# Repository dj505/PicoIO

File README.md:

# PicoIO
An affordable, simple, and feature-rich PIU controller IO board

## What is this?
The PicoIO is an extension of the [PicoFX](https://github.com/dj505/PicoFX) that's meant for building larger hand controllers or buttonboards. It's possible to build dance pads too, but as this board lacks multiplexing and is made with 5V LED lighting in mind, it's not ideal. I may design a pad IO PCB in the future, though!

**If you're not comfortable with soldering surface mount components,** there is a second board revision in the "PicoFX-THT" directory (gerbers included) that only uses through-hole components. Check the components list to see which parts are required for which PCB!

## Use cases
* Hand controller (10 buttons, 12 if you include test/service)
* Arcade buttonboard, for machines that don't already have a buttonboard (TODO - add support in firmware)
* Simple dance pad (with limitations)
    * No multiplexing support; all sensors will need to be combined into one signal
    * Limited maximum power supply for LEDs; only designed for 10-20 LEDs total, with a maximum of ~0.7A draw
        * This can be bypassed/remedied by using the expansion IO to control external LEDs with their own external power supply and some MOSFETs. I encourage you to be creative!
* Upgrade existing hand controllers, in case of broken/defective/underperforming IO

## THT vs SMD Boards
The PicoIO has two current revisions, one using surface mount components, and one using through-hole components. There are some notable differences between the two!  
* As the dense traces on the through-hole revision were a challenge to route, the traces used for LED power are thinner, which limits the maximum safe current consumption per button LED to around 0.4A or below.
* The surface mount revision of the board has much more room for routing, resulting in thicker power traces that can safely handle roughly 1.2A per button LED.
* The through-hole revision lacks debug headers, but the debug pins on the Pico are still easily accessible. This shouldn't be an issue for anyone anyway, though.

## Components
| Components (per 1 PCB) | Specs | Notes | Recommended Purchase Link | Approximate Min. Cost of Components |
|------------------------|-------|-------|---------------------------|-----------------------------------------|
|1x Raspberry Pi Pico|Any, however WiFi/Bluetooth is currently unsupported|Can be soldered with pin headers or surface mounted.|[Link](https://www.digikey.ca/en/products/detail/raspberry-pi/SC0915/13624793)|$4|
|JST XH connectors|<ul><li>10x 4 Pin</li><li>1x 6 Pin</li><li>1x 3 Pin</li><li>1x 2 Pin</li></ul>|**2.5mm pin pitch.** Designed with vertical headers in mind. Horizontal ones may work but are untested. Recommended purchase link has a minimum order number of 50-100 depending on the connector, but they're still super cheap.|<ul><li>[2 Pin](https://www.lcsc.com/product-detail/Wire-To-Board-Wire-To-Wire-Connector_HCTL-XH-2A_C3012117.html)</li><li>[3 Pin](https://www.lcsc.com/product-detail/Wire-To-Board-Wire-To-Wire-Connector_HCTL-XH-3A_C3012118.html)</li><li>[4 Pin](https://www.lcsc.com/product-detail/Wire-To-Board-Wire-To-Wire-Connector_HCTL-XH-4A_C2908602.html)</li><li>[6 Pin](https://www.lcsc.com/product-detail/Wire-To-Board-Wire-To-Wire-Connector_HCTL-XH-6A_C2908604.html)</li></ul>|$2.50|
|10x BSS138 MOSFET \*|SOT23 Package|Required for button LEDs. Recommendation - buy extras.|[Link](https://www.lcsc.com/product-detail/MOSFETs_Yangzhou-Yangjie-Elec-Tech-BSS138_C400505.html)|$0.40|
|10x 2N7002 MOSFET \*\*|TO-92 Package|Required for button LEDs.|[Link](https://www.lcsc.com/product-detail/MOSFETs_onsemi-2N7002_C124475.html)|$0.40|
|10x Resistors \*|10k Ohm, 0805 Surface Mount|Required for button LEDs. Recommendation - buy extras.|[Link](https://www.lcsc.com/product-detail/Chip-span-style-background-color-ff0-Resistor-span-Surface-Mount_Viking-Tech-AR05DTC1001_C416059.html)|$1|
|10x Resistors \*\*|10k Ohm, 1/4W Through Hole|Required for button LEDs.|[Link](https://www.lcsc.com/product-detail/Chip-span-style-background-color-ff0-Resistor-span-Surface-Mount_Viking-Tech-AR05DTC1001_C416059.html)|$1|
|1x Pin Header \*|3 pins|**Optional, only used for debugging.**|N/A|N/A|

\* Surface mount board
\*\* Through-hole board

# Instructions
Assembly is dead simple. The surface mount PCB are as follows:  
1. Solder the surface mount components.
    * Start with the BSS138 MOSFETs as they're the smallest. Use tweezers to hold them in place, tack down *one* pin with a bit of solder. It's okay if it's messy, you can clean it up after. Once it's tacked in place, solder the remaining 2 pins, then go back and clean up the first one by reflowing it after adding a bit of flux.
        * These can only go on one way, as long as they're not upside down. Make sure the pins are pointing down, not up.
    * Once done, move onto the resistors. Polarity doesn't matter here either. As with the MOSFETs, line them up with tweezers, tack down one side, solder the other side, then clean up the first side with some flux and reflowing. Easy! It's okay if they look messy, they should work just fine as long as the connection is solid.
2. Solder the Raspberry Pi Pico.
    * Gently hold it in place, tack in one or two corners to keep it held down where you want it, and solder all the pins.
    * This can be done with or without pin headers, whichever you're more comfortable with!
3. Solder the JST headers in place.
    * Keep the side with the holes facing forward, as per the printing on the silkscreen. Hold them against the PCB while soldering to make sure they're nice and even. Don't add too much solder; your joints should look like concave cones or tents, not spheres. These don't have to be perfect as long as they're solid!
4. Flash the firmware.
    * Hold down the BOOTSEL button while plugging the PicoIO into your PC. It should show up as a storage device.
    * Drag and drop your preferred .uf2 firmware file from the [releases page](https://github.com/dj505/PicoIO/releases) onto the drive.
    * It should disconnect itself after a short moment. You're good to go!

And here are the steps for the through-hole PCB:  
1. Solder the 2N7001 MOSFETs.
    * The solder points are rather clost together, but if you use flux and don't go overboard on solder, you won't have any issues.
    * Make sure they're oriented according to the silkscreen!
2. Solder the resistors.
    * These can technically go on either side of the board. If you're mounting the PCB directly against a flat surface, solder them on the top, overlapping the arrow icons. Otherwise, solder them on the bottom.
3. Solder the Raspberry Pi Pico.
    * It's easiest to solder this before the JST connectors so they don't get in the way.
    * You can choose to surface mount it or use pin headers - both work just as well.
4. Solder the JST headers in place.
    * Keep the side with the holes facing forward, as per the printing on the silkscreen. Hold them against the PCB while soldering to make sure they're nice and even. Don't add too much solder; your joints should look like concave cones or tents, not spheres. These don't have to be perfect as long as they're solid!
5. Flash the firmware.
    * Hold down the BOOTSEL button while plugging the PicoIO into your PC. It should show up as a storage device.
    * Drag and drop your preferred .uf2 firmware file from the [releases page](https://github.com/dj505/PicoIO/releases) onto the drive.
    * It should disconnect itself after a short moment. You're good to go!

## Notes
Here are some things to keep in mind:
* LEDs require a separate power input and aren't powered by the Pico itself. Pay close attention to the positive and negative polarity! It's marked on the PCB. **LEDs up to 12V are supported but the trace width only allows approximately 0.7A of current.** Don't overdo the LEDs!
    * If you're using a **reasonable number of 5V LEDs (under 500mA total draw for the entire build),** you can jump the 5V and GND pins on the 6 pin expansion port to the LED power input and power the LEDs through USB directly. **Do not** attempt to power 12V LEDs or anything requiring above 500mA this way.
* **If your LEDs don't have current limiting resistors built in, please make sure you add some!** The resistors on this PCB are just for ensuring the MOSFETs work properly.
* This kit should work equally well with 5V or 12V LEDs, but make sure you have a way to power the LEDs you pick. A reasonable number of 5V LEDs *can* be powered over USB, but pay attention to the total current draw and don't surpass the USB spec! Doing so is not recommended and would be done at your own risk. It's a good idea to just use a separate power supply or two USB cables for extra lighting.
* The legend at the top of the PCB describes the pin layout for the 10 main 4 pin button connectors. Everything else has the pins labelled beside its respective connector.
* Each MOSFET can handle up to 2A bursts if using the recommended parts, ***but*** that doesn't mean you should max them out. The trace width used allows for approximately 1.6A of total current draw which should be more than enough to light up each button. There is a second 5V pin broken out from the Pico's USB line that may be additionally used for a small number of WS2812B or similar LEDs.
* Up to 12V lighting has been tested and works without a hitch. Once again, pay close attention to polarity!

# Pinouts
Below are the pinouts for the buttons, as an easy reference in case you're playing around with the firmware.

|     PicoIO      | Raspberry Pi Pico |
|-----------------|-------------------|
|P1 down left LED |GPIO0              |
|P1 down left btn |GPIO1              |
|P2 down left LED |GPIO2              |
|P2 down left btn |GPIO3              |
|P1 up left LED   |GPIO4              |
|P1 up left btn   |GPIO5              |
|P2 up left LED   |GPIO6              |
|P2 up left btn   |GPIO7              |
|P1 center LED    |GPIO8              |
|P1 center btn    |GPIO9              |
|P2 center LED    |GPIO10             |
|P2 center btn    |GPIO11             |
|P1 up right LED  |GPIO12             |
|P1 up right btn  |GPIO13             |
|P2 up right LED  |GPIO14             |
|P2 up right btn  |GPIO15             |
|P1 down right LED|GPIO21             |
|P1 down right btn|GPIO20             |
|P2 down right LED|GPIO19             |
|P2 down right btn|GPIO18             |
|TEST             |GPIO17             |
|SERVICE          |GPIO16             |
|GP26             |GPIO26             |
|GP27             |GPIO27             |
|GP28             |GPIO28             |

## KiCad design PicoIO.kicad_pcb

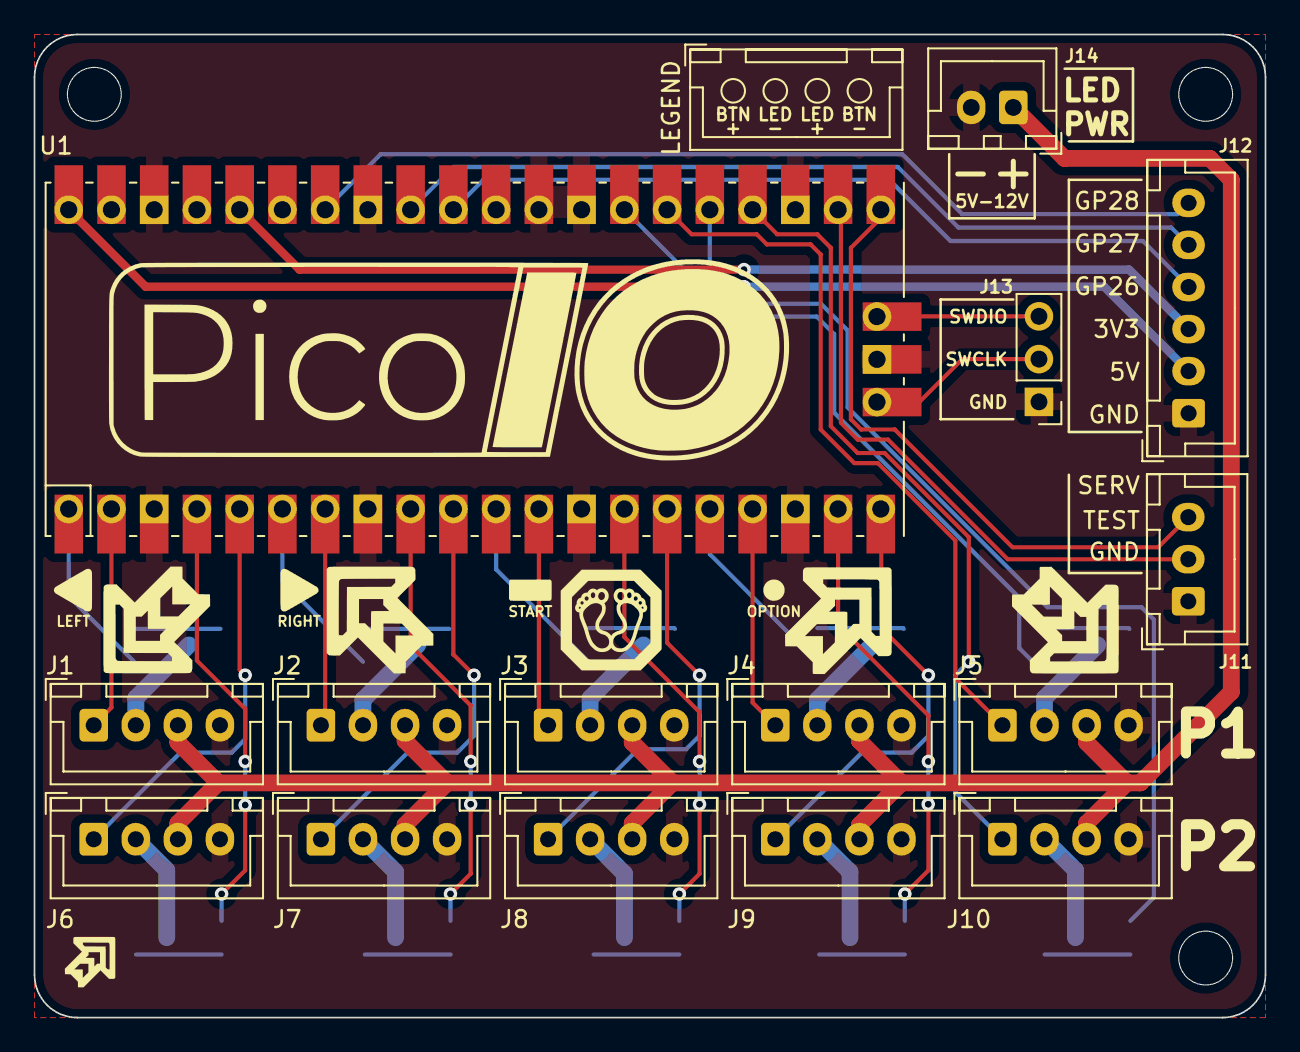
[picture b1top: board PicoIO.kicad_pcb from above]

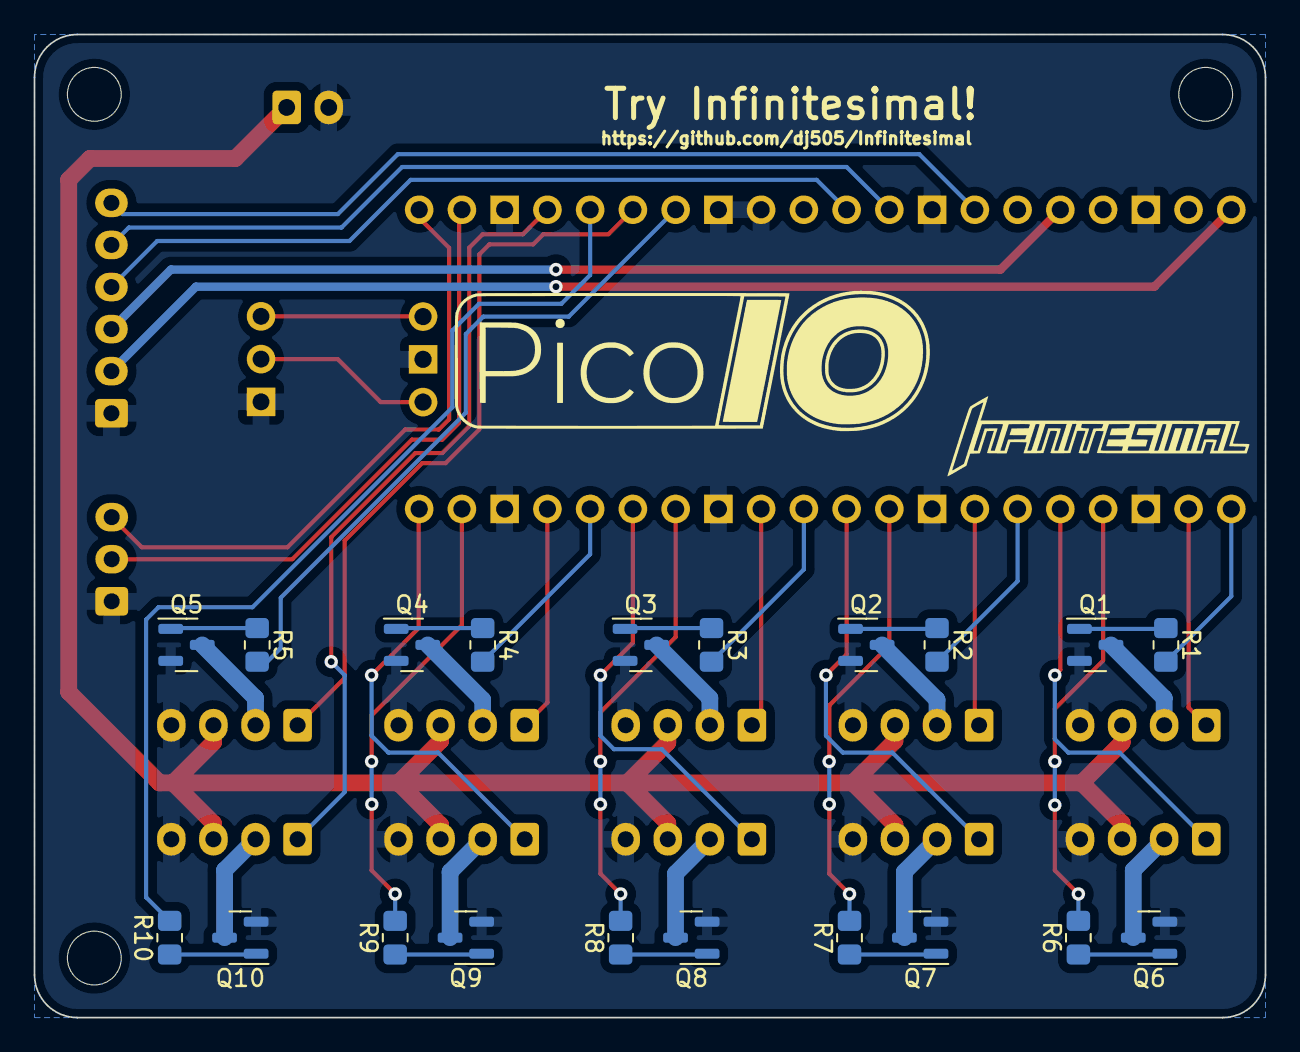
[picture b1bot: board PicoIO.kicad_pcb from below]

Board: 2 copper layers, 73.2 x 58.4 mm, 36 parts (20 on the bottom side), 51 nets.

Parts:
J1, J2, J3, J4, J4#2, J5, J6, J7, J8, J9, J10: Conn_01x04; JST_XH_B4B-XH-A_1x04_P2.50mm_Vertical
J11: Conn_01x03; JST_XH_B3B-XH-A_1x03_P2.50mm_Vertical
J12: Conn_01x06; JST_XH_B6B-XH-A_1x06_P2.50mm_Vertical
J13: Conn_01x03; PinHeader_1x03_P2.54mm_Vertical
J14: Conn_01x02; JST_XH_B2B-XH-A_1x02_P2.50mm_Vertical
Q1, Q2, Q3, Q4, Q5, Q6, Q7, Q8, Q9, Q10: BSS138; SOT-23
R1, R2, R3, R4, R5, R6, R7, R8, R9, R10: 10K; R_0805_2012Metric_Pad1.20x1.40mm_HandSolder
U1: Pico; RPi_Pico_SMD_TH

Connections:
+3V3: J12.3, U1.36 (3V3)
+5V: J12.2, U1.40 (VBUS)
GND: J1.4, J2.4, J3.4, J4#2.4, J5.4, J6.4, J7.4, J8.4, J9.4, J10.4, J11.1, J12.1, J13.1, J14.2, Q1.2 (S), Q2.2 (S), Q3.2 (S), Q4.2 (S), Q5.2 (S), Q6.2 (S), Q7.2 (S), Q8.2 (S), Q9.2 (S), Q10.2 (S), U1.3 (GND), U1.8 (GND), U1.13 (GND), U1.18 (GND), U1.23 (GND), U1.28 (GND), U1.29 (GPIO22), U1.33 (AGND), U1.38 (GND), U1.42 (GND)
GP26: J12.4, U1.31 (GPIO26_ADC0)
GP27: J12.5, U1.32 (GPIO27_ADC1)
GP28: J12.6, U1.34 (GPIO28_ADC2)
LED +: J1.3, J2.3, J3.3, J4#2.3, J5.3, J6.3, J7.3, J8.3, J9.3, J10.3, J14.1
unnamed: J1.2, Q1.3 (D)
unnamed: J2.2, Q2.3 (D)
unnamed: J3.2, Q3.3 (D)
unnamed: J4#2.2, Q4.3 (D)
unnamed: J5.2, Q5.3 (D)
unnamed: J6.2, Q6.3 (D)
unnamed: J7.2, Q7.3 (D)
unnamed: J8.2, Q8.3 (D)
unnamed: J9.2, Q9.3 (D)
unnamed: J10.2, Q10.3 (D)
unnamed: Q1.1 (G), R1.2
unnamed: Q2.1 (G), R2.2
unnamed: Q3.1 (G), R3.2
unnamed: Q4.1 (G), R4.2
unnamed: Q5.1 (G), R5.2
unnamed: Q6.1 (G), R6.2
unnamed: Q7.1 (G), R7.2
unnamed: Q8.1 (G), R8.2
unnamed: Q9.1 (G), R9.2
unnamed: Q10.1 (G), R10.2
P1 CN: J3.1, U1.12 (GPIO9)
P1 CN LED: R3.1, U1.11 (GPIO8)
P1 DL: J1.1, U1.2 (GPIO1)
P1 DL LED: R1.1, U1.1 (GPIO0)
P1 DR: J5.1, U1.26 (GPIO20)
P1 DR LED: R5.1, U1.27 (GPIO21)
P1 UL: J2.1, U1.7 (GPIO5)
P1 UL LED: R2.1, U1.6 (GPIO4)
P1 UR: J4#2.1, U1.17 (GPIO13)
P1 UR LED: R4.1, U1.16 (GPIO12)
P2 CN: J8.1, U1.15 (GPIO11)
P2 CN LED: R8.1, U1.14 (GPIO10)
P2 DL: J6.1, U1.5 (GPIO3)
P2 DL LED: R6.1, U1.4 (GPIO2)
P2 DR: J10.1, U1.24 (GPIO18)
P2 DR LED: R10.1, U1.25 (GPIO19)
P2 UL: J7.1, U1.10 (GPIO7)
P2 UL LED: R7.1, U1.9 (GPIO6)
P2 UR: J9.1, U1.20 (GPIO15)
P2 UR LED: R9.1, U1.19 (GPIO14)
SERVICE: J11.3, U1.21 (GPIO16)
SWCLK: J13.2, U1.41 (SWCLK)
SWDIO: J13.3, U1.43 (SWDIO)
TEST: J11.2, U1.22 (GPIO17)

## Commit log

2023-01-04 Schematic
2023-01-05 PCB revision 1 (NOT READY FOR USE)
2023-01-05 Add MOSFETs, move to 4 pin JST, DRC passed
2023-01-05 External LED power, some routing/aesthetic changes
2023-01-05 Add buttonboard icons to PCB, generate gerber
2023-01-05 Extremely minor alignment nitpick
2023-01-06 More small nitpicks
2023-01-06 Final logo placement, regenerate gerber files
2023-01-23 Add through-hole board revision, update README
2023-01-23 Thicken traces on SMD ver. PCB
2023-01-23 Remove leftover vias
2023-01-23 Thicken power traces on SMD rev., update README
2023-02-20 Add pinouts to readme
